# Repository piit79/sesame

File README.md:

# Sesame

[![CC BY-NC-SA 4.0][cc-by-nc-sa-shield]][cc-by-nc-sa]

### Alice like ergo keyboard using only THT parts

Modified by [u/piit79](https://reddit.com/user/piit79) to use components more in line
with other similar kits (Mysterium etc.).

### Partslist
 |Count|Part|Reference|LCSC Part #|
 |-|-|-|-|
 |1|ATmega32A 40 pin DIP (32L works too)|U1|C12703|
 |1|40 pin DIP socket (optional but highly recommended)|U1|C2332|
 |1|USB4085-GF-A USB Type-C socket|USB1|
 |1|500 mA polyfuse|F1|C369081|
 |2|6mm momentary push buttons|Boot,Reset|C620202|
 |1|16 MHz quartz crystal|XTAL1|C16212|
 |1|4.7 uF electrolytic capacitor|C1|C47879|
 |2|100 nF ceramic disk capacitor|C2,C3|C353913|
 |2|22 pF ceramic disk capacitor|C4,C5|C254096|
 |1|1.5 kΩ resistor|R1|C58620|
 |2|75 Ω resistor|R2,R3|C433693|
 |2|5.1 kΩ resistor|R4,R5|C714593|
 |1|10 kΩ resistor|R6|C119347|
 |2|3.6 V zener diode (DO-35 BZX55C3V6)|D1,D2|C2508|
 |66|universal switching diode (DO-35 1N4148)|D3-D68|C14516|
 
 The USB port can be found here:  
https://www.digikey.com/en/products/detail/gct/USB4085-GF-A/9859733

-----

This work is licensed under a
[Creative Commons Attribution-NonCommercial-ShareAlike 4.0 International License][cc-by-nc-sa].

[![CC BY-NC-SA 4.0][cc-by-nc-sa-image]][cc-by-nc-sa]

[cc-by-nc-sa]: http://creativecommons.org/licenses/by-nc-sa/4.0/
[cc-by-nc-sa-image]: https://licensebuttons.net/l/by-nc-sa/4.0/88x31.png
[cc-by-nc-sa-shield]: https://img.shields.io/badge/License-CC%20BY--NC--SA%204.0-lightgrey.svg

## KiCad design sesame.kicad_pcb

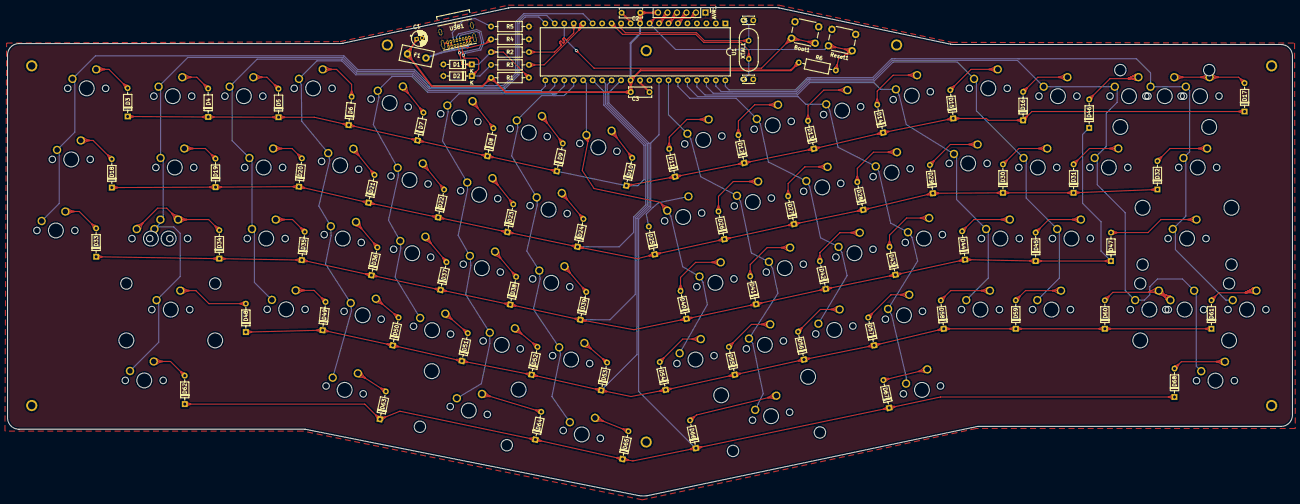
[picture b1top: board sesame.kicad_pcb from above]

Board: 2 copper layers, 344.4 x 130.9 mm, 155 parts (0 on the bottom side), 102 nets.

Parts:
AVR1: Conn_01x06; PinHeader_1x06_P2.54mm_Vertical
Boot1: Boot; SW_PUSH_6mm
C1: 4.7u; CP_Radial_D4.0mm_P1.50mm
C2, C3: 0.1u; C_Disc_D6.0mm_W2.5mm_P5.00mm
C4, C5: 22p; C_Disc_D3.0mm_W2.0mm_P2.50mm
D1, D2: 3.6V; D_DO-35_SOD27_P7.62mm_Horizontal
D3, D4, D5, D6, D7, D8, D9, D10, D11, D12, D13, D14, D15, D16, D17, D18, D19, D20, D21, D22, D23, D24, D25, D26, D27, D28, D29, D30, D31, D32, D33, D34, D35, D36, D37, D38, D39, D40, D41, D42, D43, D44, D45, D46, D47, D48, D49, D50, D51, D52, D53, D54, D55, D56, D57, D58, D59, D60, D61, D62, D63, D64, D65, D66, D67, D68: D_Small; D_DO-35_SOD27_P7.62mm_Horizontal
F1: 500mA; Fuse_Littelfuse_395Series
MX1: ESC; MXOnly-1U-NoLED
MX2: 1; MXOnly-1U-NoLED
MX3: 2; MXOnly-1U-NoLED
MX4: 3; MXOnly-1U-NoLED
MX5: 4; MXOnly-1U-NoLED
MX6: 5; MXOnly-1U-NoLED
MX7: 6; MXOnly-1U-NoLED
MX8: 7; MXOnly-1U-NoLED
MX9: 8; MXOnly-1U-NoLED
MX10: 9; MXOnly-1U-NoLED
MX11: 0; MXOnly-1U-NoLED
MX12: minus; MXOnly-1U-NoLED
MX13: plus; MXOnly-1U-NoLED
MX14: clear; MXOnly-1U-NoLED
MX15: MX-NoLED; MXOnly-2U-NoLED
MX16, MX17, MX19, MX20, MX21, MX22, MX23, MX24, MX25, MX26, MX27, MX28, MX29, MX30, MX32, MX34, MX35, MX36, MX37, MX38, MX39, MX40, MX41, MX42, MX43, MX44, MX45, MX48, MX49, MX50, MX51, MX52, MX53, MX54, MX55, MX56, MX57, MX58, MX60, MX62, MX63, MX67, MX68: MX-NoLED; MXOnly-1U-NoLED
MX18, MX31: MX-NoLED; MXOnly-1.5U-NoLED
MX33, MX59: MX-NoLED; MXOnly-1.75U-NoLED
MX46: MX-NoLED; MXOnly-2.25U-ReversedStabilizers-NoLED
MX47: MX-NoLED; MXOnly-2.25U-NoLED
MX61: MX-NoLED; MXOnly-2.75U-NoLED
MX64: MX-NoLED; MXOnly-2U-ReversedStabilizers-NoLED
MX65, MX69: MX-NoLED; MXOnly-1.25U-NoLED
MX66: bkspc; MXOnly-2.25U-ReversedStabilizers-NoLED
R1: 1.5K; R_Axial_DIN0207_L6.3mm_D2.5mm_P10.16mm_Horizontal
R2, R3: 68R; R_Axial_DIN0207_L6.3mm_D2.5mm_P10.16mm_Horizontal
R4, R5: 5.1K; R_Axial_DIN0207_L6.3mm_D2.5mm_P10.16mm_Horizontal
R6: 10k; R_Axial_DIN0207_L6.3mm_D2.5mm_P10.16mm_Horizontal
Reset1: Reset; SW_PUSH_6mm
U1: ATmega32A-PU; DIP-40_W15.24mm
USB1: USB_C_Receptacle_USB2.0; USB_C_GCT_USB4085
XTAL1: Crystal; Crystal_HC49-4H_Vertical

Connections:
+5V: AVR1.6, C1.1, C2.1, C3.1, F1.1, R1.1, R6.1, U1.10, U1.30
BOOT: Boot1.2, U1.18
D+: R3.2, U1.16
D-: R2.2, U1.17
GND: AVR1.1, Boot1.1, C1.2, C2.2, C3.2, C4.1, C5.1, D1.2, D2.2, R4.2, R5.2, Reset1.1, U1.11, U1.31, USB1.A1, USB1.A12, USB1.B1, USB1.B12, USB1.S1
MISO: AVR1.3, U1.7
MOSI: AVR1.2, U1.6
unnamed: C4.2, U1.13, XTAL1.2
unnamed: C5.2, U1.12, XTAL1.1
unnamed: D1.1, R1.2, R2.1, USB1.A7, USB1.B7
unnamed: D2.1, R3.1, USB1.A6, USB1.B6
unnamed: D3.2, MX1.2
unnamed: D4.2, MX2.2
unnamed: D5.2, MX3.2
unnamed: D6.2, MX4.2
unnamed: D7.2, MX5.2
unnamed: D8.2, MX6.2
unnamed: D9.2, MX7.2
unnamed: D10.2, MX8.2
unnamed: D11.2, MX9.2
unnamed: D12.2, MX10.2
unnamed: D13.2, MX11.2
unnamed: D14.2, MX12.2
unnamed: D15.2, MX13.2
unnamed: D16.2, MX14.2
unnamed: D18.2, MX17.2
unnamed: D19.2, MX18.2
unnamed: D20.2, MX19.2
unnamed: D21.2, MX20.2
unnamed: D22.2, MX21.2
unnamed: D23.2, MX22.2
unnamed: D24.2, MX23.2
unnamed: D25.2, MX24.2
unnamed: D26.2, MX25.2
unnamed: D27.2, MX26.2
unnamed: D28.2, MX27.2
unnamed: D29.2, MX28.2
unnamed: D30.2, MX29.2
unnamed: D31.2, MX30.2
unnamed: D32.2, MX31.2
unnamed: D33.2, MX32.2
unnamed: D35.2, MX34.2
unnamed: D36.2, MX35.2
unnamed: D37.2, MX36.2
unnamed: D38.2, MX37.2
unnamed: D39.2, MX38.2
unnamed: D40.2, MX39.2
unnamed: D41.2, MX40.2
unnamed: D42.2, MX41.2
unnamed: D43.2, MX42.2
unnamed: D44.2, MX43.2
unnamed: D45.2, MX44.2
unnamed: D46.2, MX45.2
unnamed: D47.2, MX46.2
unnamed: D48.2, MX47.2
unnamed: D49.2, MX48.2
unnamed: D50.2, MX49.2
unnamed: D51.2, MX50.2
unnamed: D52.2, MX51.2
unnamed: D53.2, MX52.2
unnamed: D54.2, MX53.2
unnamed: D55.2, MX54.2
unnamed: D56.2, MX55.2
unnamed: D57.2, MX56.2
unnamed: D58.2, MX57.2
unnamed: D59.2, MX58.2
unnamed: D61.2, MX60.2
unnamed: D62.2, MX62.2
unnamed: D63.2, MX63.2
unnamed: D64.2, MX64.2
unnamed: D65.2, MX65.2
unnamed: D66.2, MX66.2
unnamed: D67.2, MX67.2
unnamed: D68.2, MX68.2
unnamed: R4.1, USB1.A5
unnamed: R5.1, USB1.B5
RST: AVR1.5, R6.2, Reset1.2, U1.9
SCK: AVR1.4, U1.8
VCC: F1.2, USB1.A4, USB1.A9, USB1.B4, USB1.B9
bs: D17.2, MX15.2, MX16.2
caps: D34.2, MX33.2, MX69.1
col0: MX1.1, MX17.1, MX32.1, U1.15
col1: MX2.1, MX18.1, MX33.1, MX47.1, MX62.1, MX69.2, U1.19
col2: MX3.1, MX19.1, MX34.1, MX48.1, U1.20
col3: MX4.1, MX20.1, MX35.1, MX49.1, MX63.1, U1.21
col4: MX5.1, MX21.1, MX36.1, MX50.1, U1.22
col5: MX6.1, MX22.1, MX37.1, MX51.1, MX64.1, U1.23
col6: MX7.1, MX23.1, MX38.1, MX52.1, MX65.1, U1.24
col7: MX8.1, MX24.1, MX39.1, MX53.1, U1.25
col8: MX9.1, MX25.1, MX40.1, MX54.1, MX66.1, U1.34
col9: MX10.1, MX26.1, MX41.1, MX55.1, U1.35
col10: MX11.1, MX27.1, MX42.1, MX56.1, MX67.1, U1.36
col11: MX12.1, MX28.1, MX43.1, MX57.1, U1.37
col12: MX13.1, MX29.1, MX44.1, MX58.1, U1.38
col13: MX14.1, MX30.1, MX45.1, MX59.1, MX61.2, MX68.1, U1.39
col14: MX15.1, MX16.1, MX31.1, MX46.1, MX60.1, U1.40
row0: D3.1, D4.1, D5.1, D6.1, D7.1, D8.1, D9.1, D10.1, D11.1, D12.1, D13.1, D14.1, D15.1, D16.1, D17.1, U1.26
row1: D18.1, D19.1, D20.1, D21.1, D22.1, D23.1, D24.1, D25.1, D26.1, D27.1, D28.1, D29.1, D30.1, D31.1, D32.1, U1.27
row2: D33.1, D34.1, D35.1, D36.1, D37.1, D38.1, D39.1, D40.1, D41.1, D42.1, D43.1, D44.1, D45.1, D46.1, D47.1, U1.28
row3: D48.1, D49.1, D50.1, D51.1, D52.1, D53.1, D54.1, D55.1, D56.1, D57.1, D58.1, D59.1, D60.1, D61.1, U1.29
row4: D62.1, D63.1, D64.1, D65.1, D66.1, D67.1, D68.1, U1.33
rs: D60.2, MX59.2, MX61.1

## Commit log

2021-04-16 Use components more in line with other similar kits (Mysterium etc.)
2021-04-16 Add gerber zip files
